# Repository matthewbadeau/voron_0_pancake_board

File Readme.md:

# Pancake Board

## Incomplete forked project

Needs review

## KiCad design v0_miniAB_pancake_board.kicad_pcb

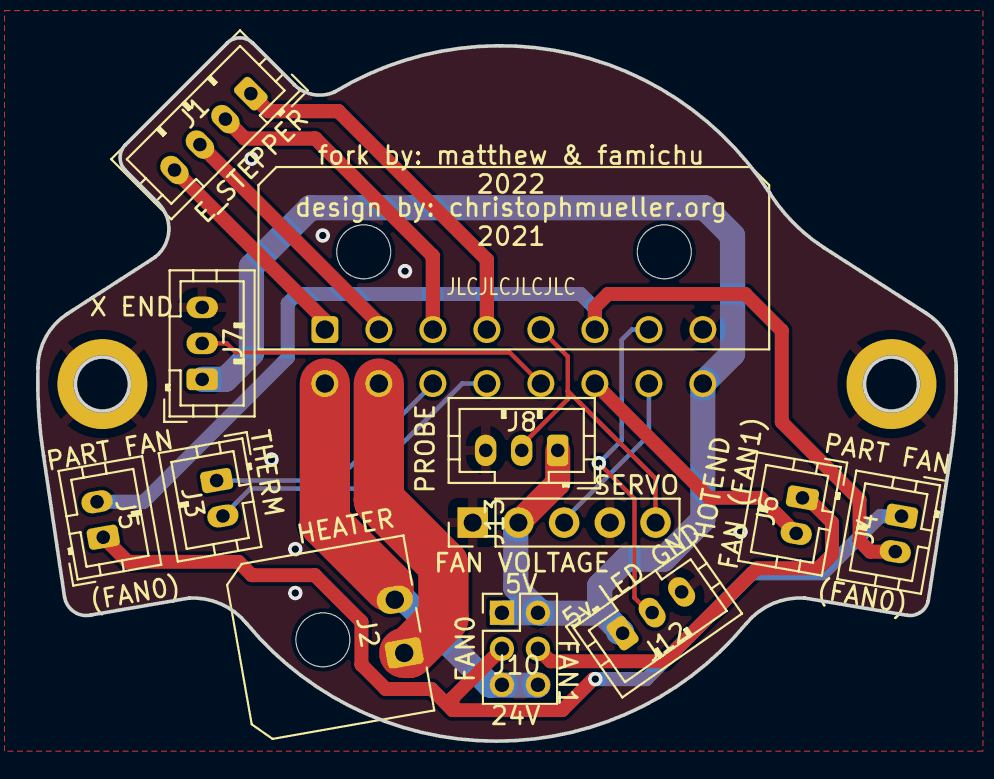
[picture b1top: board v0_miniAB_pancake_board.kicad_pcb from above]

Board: 2 copper layers, 51.0 x 39.1 mm, 14 parts (0 on the bottom side), 18 nets.

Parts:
H1, H2: MountingHole_Pad; MountingHole_3.2mm_M3_Pad
J1: E_STEPPER; JST_PH_B4B-PH-K_1x04_P2.00mm_Vertical
J2: HEATER; Molex_Micro-Fit_3.0_43650-0200_1x02_P3.00mm_Horizontal
J3: THERM; JST_PH_B2B-PH-K_1x02_P2.00mm_Vertical
J4, J5: PART FAN; JST_PH_B2B-PH-K_1x02_P2.00mm_Vertical
J6: HOTEND FAN; JST_PH_B2B-PH-K_1x02_P2.00mm_Vertical
J7: ENDSTOP0; JST_PH_B3B-PH-K_1x03_P2.00mm_Vertical
J8: ENDSTOP1; JST_PH_B3B-PH-K_1x03_P2.00mm_Vertical
J9: Breakout Molex Micro-fit 3.0 02x08; Molex_Micro-Fit_3.0_43045-1600_2x08_P3.00mm_Horizontal
J10: FAN0_V_JUMPER; PinHeader_2x03_P2.00mm_Vertical
J12: RGB LED; JST_PH_B3B-PH-K_1x03_P2.00mm_Vertical
J13: BLTOUCH; PinHeader_1x05_P2.54mm_Vertical

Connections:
+5V: J7.1, J8.1, J9.16, J10.1, J10.2, J12.1, J13.2
+24V: J2.2, J9.9, J10.5, J10.6
/A+: J1.4, J9.1
/A-: J1.3, J9.2
/B+: J1.2, J9.3
/B-: J1.1, J9.4
/VFAN0: J4.1, J5.1, J10.3
/VFAN1: J6.1, J10.4
/fan0: J4.2, J5.2, J9.6
/fan1: J6.2, J9.14
/heat_gnd: J2.1, J9.10
/led: J9.7, J12.2
/servo: J9.15, J13.3
/sw0: J7.2, J9.13
/sw1: J8.2, J9.5, J13.5
/therm0: J3.1, J9.11
/therm1: J3.2, J9.12
GND: H1.1, H2.1, J7.3, J8.3, J9.8, J12.3, J13.1, J13.4

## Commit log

2022-03-03 Initial fork commit
    Some quick changes to get started.
2022-03-03 Added traces, pushing for review.
    Please review
2022-03-03 Adjusted after comments
    Fixed some pin orientations and pin assignments in the schematic.
2022-03-03 Add @famichu as co-designer
2022-03-03 Silkscreen changes
2022-03-03 Minor silkscreen change
2022-03-03 Silkscreen change and gerber uploads
2022-03-03 Remove backup files
2022-03-03 Fix connectors direction and organize routes
2022-03-03 Adding via and moving JLCJLC placeholder text
2022-03-14 Fixing safety issues
    * The heater connector was at an angle that could cause cable interference with the X endstop on the V0
    * The fan voltage selector is now a 2x3 pin connector
    * The X end stop position was switched -- now fixed
2022-03-14 Fixing Silkscreen
